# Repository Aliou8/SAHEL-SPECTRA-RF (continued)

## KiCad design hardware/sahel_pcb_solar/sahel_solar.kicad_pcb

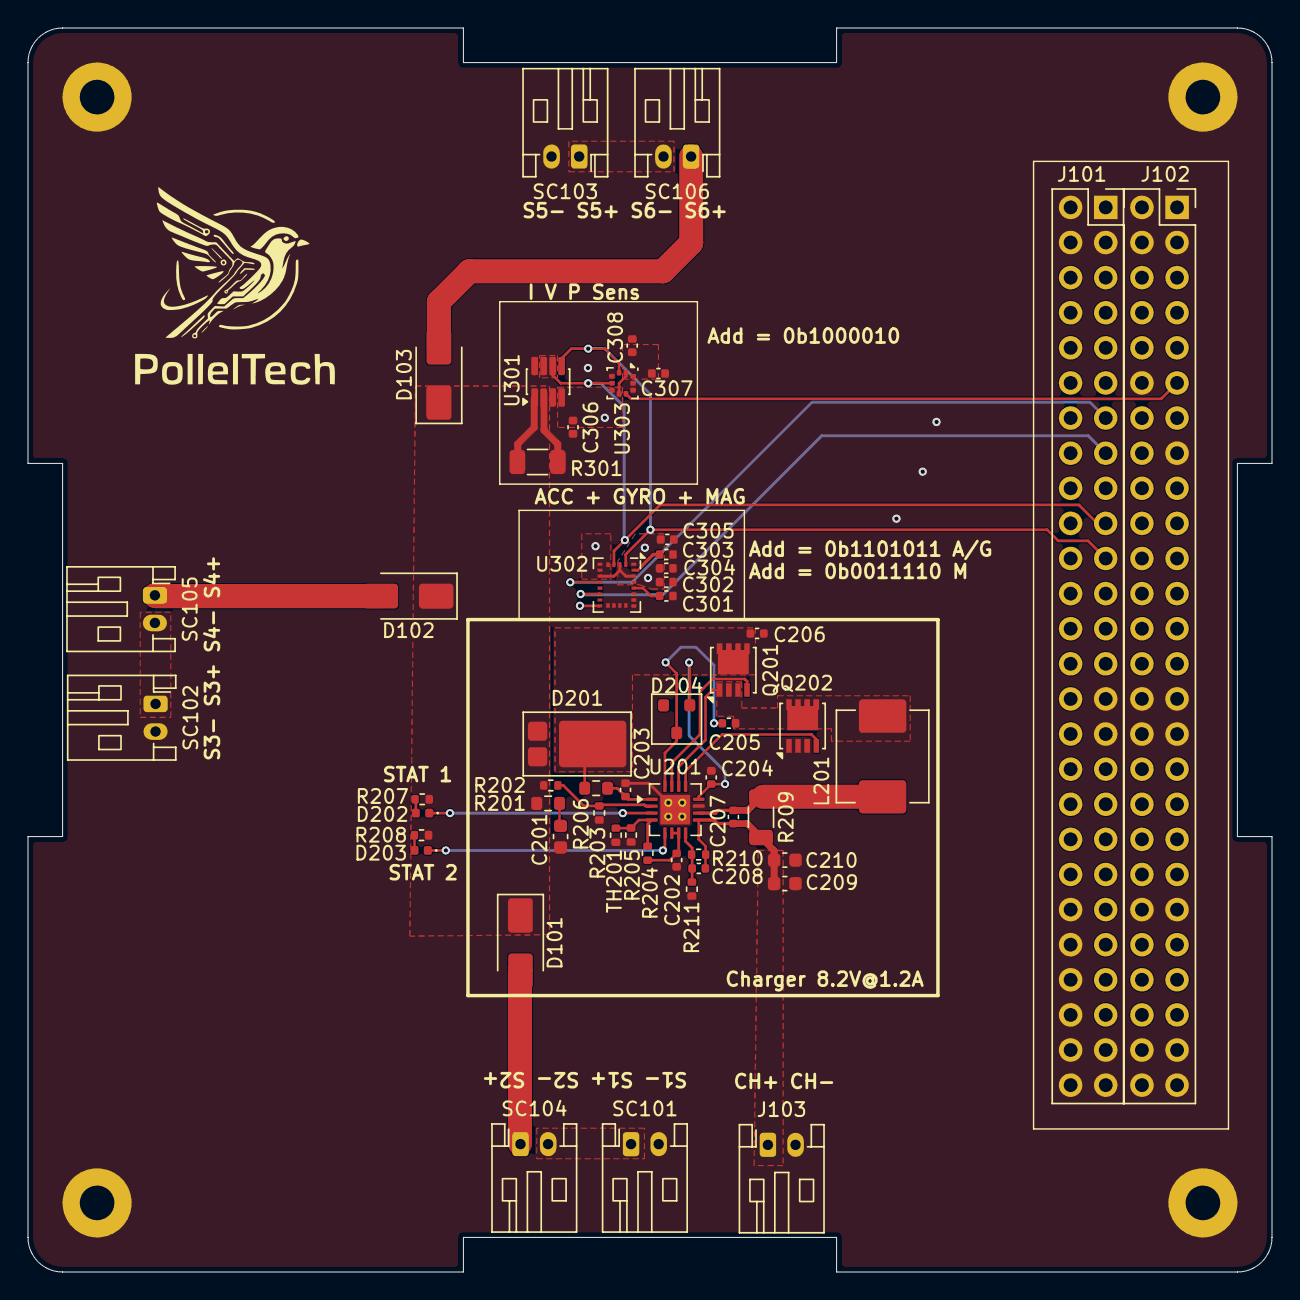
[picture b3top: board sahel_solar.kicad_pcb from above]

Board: 2 copper layers, 90.0 x 90.0 mm, 58 parts (0 on the bottom side), 34 nets.

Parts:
C201: 2.2u; C_0603_1608Metric
C202, C203, C204, C205, C206, C207, C302, C303, C305: 0.1u; C_0402_1005Metric
C208: 22p; C_0402_1005Metric
C209, C210: 10u; C_0603_1608Metric
C301: 10n; C_0402_1005Metric
C304: 10u; C_0402_1005Metric
C306, C307, C308: 1u; C_0402_1005Metric
D101, D102, D103: SS110; D_SMA
D201: PDS3100; D_PowerDI-5
D202: LED_S1; LED_0402_1005Metric
D203: LED_S2; LED_0402_1005Metric
D204: BAT54; SOT-23
H301, H302, H303, H304: MountingHole_Pad; MountingHole_2.5mm_Pad
J101, J102: Conn_02x26_Odd_Even; PinSocket_2x26_P2.54mm_Vertical
J103: charge; JST_PH_S2B-PH-K_1x02_P2.00mm_Horizontal
L201: 4.7u; L_Vishay_IHLP-2525
Q201, Q202: SiS454DN; Vishay_PowerPAK_1212-8_Single
R201: 2; R_0603_1608Metric
R202: 650k; R_0402_1005Metric
R203, R211: 100k; R_0402_1005Metric
R204: 9.31k; R_0402_1005Metric
R205: 430k; R_0402_1005Metric
R206: 10; R_0603_1608Metric
R207, R208: 10k; R_0402_1005Metric
R209, R301: 10m; R_1206_3216Metric
R210: 290k; R_0402_1005Metric
SC101, SC102, SC103, SC104, SC105, SC106: Solar_Cell; JST_PH_S2B-PH-K_1x02_P2.00mm_Horizontal
TH201: NTC; R_0402_1005Metric
U201: BQ24650; Texas_RVA_VQFN-16-1EP_3.5x3.5mm_P0.5mm_EP2.14x2.14mm_Therma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
U301: INA219AxDCN; SOT-23-8
U302: LSM9DS1; LGA-24L_3x3.5mm_P0.43mm
U303: LPS22HH; ST_HLGA-10_2x2mm_P0.5mm_LayoutBorder3x2y

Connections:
+3.3V: C302.1, C304.1, C305.1, C306.1, C307.1, C308.1, J101.5, J101.6, J101.11, J101.12, J101.17, J101.18, J101.23, J101.27, J101.28, J101.30, J101.33, J101.40, J101.47, J102.9, J102.10, J102.18, J102.21, J102.23, J102.25, J102.27, J102.28, J102.37, J102.38, J102.47, J102.48, U301.4 (VS), U302.1 (VDDIO), U302.3 (VDDIO), U302.5 (SDO_A/G), U302.6 (SDO_M), U302.7 (CS_A/G), U302.8 (CS_M), U302.13 (DEN_A/G), U302.22 (VDD), U302.23 (VDD), U303.1 (Vdd_IO), U303.5 (SA0), U303.6 (~CS), U303.10 (VDD)
/BUS_SCL: J101.21, U301.5 (SCL), U302.2 (SCL/SPC), U303.2 (SCL)
/BUS_SDA: J101.19, U301.6 (SDA), U301.7 (A0), U302.4 (SDA/SDI/SDO), U303.4 (SDA)
/CHARGER/LODRV: Q202.4 (G), U201.13 (LODRV)
/CHARGER/Pack+: C207.2, C208.2, C209.2, C210.2, J103.1, R209.2, R210.1, U201.9 (SRN)
/CHARGER/TS: R204.2, R205.1, TH201.1, U201.4 (TS)
/CHARGER/VFB: C208.1, R210.2, R211.1, U201.8 (VFB)
/DRDY_INT_B: J102.11, U303.7 (INT_DRDY)
/DRDY_M: J101.13, U302.9 (DRDY_M)
/INT_A/G: J101.15, U302.11 (INT1_A/G)
/SOLAR+: D101.1 (K), D102.1 (K), D103.1 (K), D201.2 (A), R201.2, R202.1, R207.2, R208.2, R301.2, U301.1 (IN+)
GND: C201.1, C202.1, C203.1, C204.1, C206.1, C209.1, C210.1, C301.2, C302.2, C303.2, C304.2, C305.2, C306.2, C307.2, C308.2, H301.1 (1_1), H302.1 (1_1), H303.1 (1_1), H304.1 (1_1), J101.1, J101.2, J101.3, J101.4, J101.29, J101.31, J101.42, J101.44, J101.46, J101.48, J101.49, J101.50, J101.51, J101.52, J102.1, J102.2, J102.3, J102.4, J102.12, J102.15, J102.29, J102.30, J102.31, J102.32, J102.41, J102.42, J102.49, J102.50, J102.51, J102.52, J103.2, Q202.1 (S), Q202.2 (S), Q202.3 (S), R203.2, R205.2, R211.2, R301.1, SC101.2 (-), SC102.2 (-), SC103.2 (-), TH201.2, U201.11 (GND), U201.17 (GND), U301.2 (IN-), U301.3 (GND), U301.8 (A1), U302.14 (RES), U302.15 (RES), U302.16 (RES), U302.17 (RES), U302.18 (RES), U302.19 (GND), U302.20 (GND), U303.3 (GND), U303.8 (GND), U303.9 (GND)
unnamed: C201.2, R201.1
unnamed: D101.2 (A), SC104.1 (+)
unnamed: D102.2 (A), SC105.1 (+)
unnamed: D103.2 (A), SC106.1 (+)
unnamed: C206.2, D201.1 (K), Q201.5 (D), R206.1
unnamed: D202.2 (A), R207.1
unnamed: D202.1 (K), U201.3 (STAT1)
unnamed: D203.2 (A), R208.1
unnamed: D203.1 (K), U201.5 (STAT2)
unnamed: C204.2, D204.1 (A), U201.12 (REGN)
unnamed: C205.1, D204.3 (K), U201.16 (BTST)
unnamed: Q201.4 (G), U201.15 (HIDRV)
unnamed: C205.2, L201.1, Q201.1 (S), Q201.2 (S), Q201.3 (S), Q202.5 (D), U201.14 (PH)
unnamed: SC101.1 (+), SC104.2 (-)
unnamed: SC102.1 (+), SC105.2 (-)
unnamed: SC103.1 (+), SC106.2 (-)
unnamed: R202.2, R203.1, U201.2 (MPPSET)
unnamed: C207.1, L201.2, R209.1, U201.10 (SRP)
unnamed: C202.2, R204.1, U201.6 (VREF), U201.7 (TERM_EN)
unnamed: C203.2, R206.2, U201.1 (VCC)
unnamed: C303.1, U302.24 (C1)
unnamed: C301.1, U302.21 (CAP)

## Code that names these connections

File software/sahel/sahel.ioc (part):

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Mcu.Name=STM32H7B0VBTx
Mcu.Package=LQFP100
Mcu.UserName=STM32H7B0VBTx
PA0.GPIOParameters=GPIO_Label
PA0.GPIO_Label=RF_EN
PA0.Signal=GPIO_Output
PA1.GPIOParameters=GPIO_Label
PA1.GPIO_Label=LED1
PA1.Signal=GPIO_Output
PA11.Mode=Host_FS
PA11.Signal=USB_OTG_HS_DM
PA12.Mode=Host_FS
PA12.Signal=USB_OTG_HS_DP
PA13.Mode=Trace_Asynchronous_SW
PA13.Signal=DEBUG_JTMS-SWDIO
PA14.Mode=Trace_Asynchronous_SW
PA14.Signal=DEBUG_JTCK-SWCLK
PA15.GPIOParameters=GPIO_Label
PA15.GPIO_Label=CAN_SHDN
PA15.Signal=GPIO_Output
PA2.GPIOParameters=GPIO_Label
PA2.GPIO_Label=LED2
PA2.Signal=GPIO_Output
PA3.GPIOParameters=GPIO_Label
PA3.GPIO_Label=LED3
PA3.Signal=GPIO_Output
PA4.Mode=NSS_Signal_Hard_Output
PA4.Signal=SPI1_NSS
PA5.Mode=Full_Duplex_Master
PA5.Signal=SPI1_SCK
PA6.Mode=Full_Duplex_Master
PA6.Signal=SPI1_MISO
PA7.Mode=Full_Duplex_Master
PA7.Signal=SPI1_MOSI
PA8.Mode=I2C
PA8.Signal=I2C3_SCL
PA9.GPIOParameters=GPIO_Label
PA9.GPIO_Label=FRAM_WP
PA9.Signal=GPIO_Output
PB10.GPIOParameters=GPIO_Label
PB10.GPIO_Label=VHF_GPIO1
PB10.Signal=GPIO_Output
PB12.Mode=NSS_Signal_Hard_Output
PB12.Signal=SPI2_NSS
PB13.Mode=Full_Duplex_Master
PB13.Signal=SPI2_SCK
PB14.Mode=Full_Duplex_Master
PB14.Signal=SPI2_MISO
PB15.Mode=Full_Duplex_Master
PB15.Signal=SPI2_MOSI
PB3.Mode=Trace_Asynchronous_SW
PB3.Signal=DEBUG_JTDO-SWO
PB4.GPIOParameters=GPIO_Label
PB4.GPIO_Label=RTC_EVI
PB4.Signal=GPIO_Output
PB5.GPIOParameters=GPIO_Label
PB5.GPIO_Label=RTC_INT
PB5.Signal=GPIO_Output
PB6.Mode=I2C
PB6.Signal=I2C1_SCL
PB7.Mode=I2C
PB7.Signal=I2C1_SDA
PC14-OSC32_IN.Mode=LSE-External-Clock-Source
PC14-OSC32_IN.Signal=RCC_OSC32_IN
PC4.GPIOParameters=GPIO_Label
PC4.GPIO_Label=UHF_GPIO1
PC4.Signal=GPIO_Output
PC5.GPIOParameters=GPIO_Label
PC5.GPIO_Label=UHF_GPIO2
PC5.Signal=GPIO_Output
PC9.Mode=I2C
PC9.Signal=I2C3_SDA
PD0.Mode=FDCAN_Activate
PD0.Signal=FDCAN1_RX
PD1.Mode=FDCAN_Activate
PD1.Signal=FDCAN1_TX
PD12.Mode=I2C
PD12.Signal=I2C4_SCL
PD13.Mode=I2C
PD13.Signal=I2C4_SDA
PD14.Mode=Asynchronous
PD14.Signal=UART9_RX
PD15.Mode=Asynchronous
PD15.Signal=UART9_TX
PD2.GPIOParameters=GPIO_Label
PD2.GPIO_Label=CAN_STB
PD2.Signal=GPIO_Output
PD4.Mode=Hardware Flow Control (RS485)
PD4.Signal=USART2_DE
PD5.Mode=Asynchronous
PD5.Signal=USART2_TX
PD6.Mode=Asynchronous
PD6.Signal=USART2_RX
PD8.GPIOParameters=GPIO_Label
PD8.GPIO_Label=SPI_CS2
PD8.Signal=GPIO_Output
PD9.GPIOParameters=GPIO_Label
PD9.GPIO_Label=SPI_CS3
PD9.Signal=GPIO_Output
PE11.Mode=NSS_Signal_Hard_Output
PE11.Signal=SPI4_NSS
PE12.Mode=Full_Duplex_Master
PE12.Signal=SPI4_SCK
PE13.Mode=Full_Duplex_Master
PE13.Signal=SPI4_MISO
PE14.Mode=Full_Duplex_Master
PE14.Signal=SPI4_MOSI
PE15.GPIOParameters=GPIO_Label
PE15.GPIO_Label=VHF_GPIO2
PE15.Signal=GPIO_Output
PH0-OSC_IN.Mode=HSE-External-Oscillator
PH0-OSC_IN.Signal=RCC_OSC_IN
PH1-OSC_OUT.Mode=HSE-External-Oscillator
PH1-OSC_OUT.Signal=RCC_OSC_OUT
RCC.HSE_VALUE=8000000
RCC.SYSCLKFreq_VALUE=280000000
RCC.SYSCLKSource=RCC_SYSCLKSOURCE_PLLCLK
board=custom

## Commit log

2026-05-09 feat(hardware): complete major CubeSat hardware milestone
    Finalize most PCB designs for OBC, radio, power, and solar interfaces
    Complete main mechanical structure design of the CubeSat
    Generate STM32CubeMXIDE software project for STM32H7 platform
    Prepare hardware/software integration baseline for future development
2026-05-09 docs: advance README documentation
2026-05-10 docs: advance README documentation
    Remove KiCad project files for sahel_pcb and its subprojects, indicating a clean slate for future development. Mark subprojects as dirty to reflect uncommitted changes.
2026-05-11 docs: advance README documentation
    Refactor code structure for improved readability and maintainability
2026-05-16 Add support for Sahel STM32H7B0 board and associated drivers
    - Created device tree source (DTS) file for Sahel STM32H7B0 board with configurations for GPIO, UART, SPI, I2C, CAN, and various sensors.
    - Added YAML configuration for the Sahel STM32H7B0 board, specifying memory and supported features.
    - Introduced default configuration file for the board enabling MPU, stack protection, and GPIO.
    - Implemented CMake and Kconfig files for BQ76907 battery protection module, including driver source and bindings.
    - Added CC1125 radio transceiver module with necessary configurations and driver files.
    - Integrated FM24CL64B I2C FRAM module with complete driver implementation and device tree bindings.
2026-05-19 Add BQ76907 driver implementation and remove CC1125 module
    - Implemented the BQ76907 driver in `bq76907.h` with necessary data structures, error codes, and sensor channels.
    - Updated device tree bindings for BQ76907 in `ti,bq76907.yml` to include new properties for voltage and current thresholds.
    - Removed the CC1125 module, including its drivers, Kconfig, and device tree bindings, as it is no longer needed.
    - Added a Kconfig dependency for EEPROM in the FM24CL64B driver.
    - Created a new README.md file for documentation purposes.
2026-05-19 chore: bump version to v0.0.2
2026-05-19 Refactor code structure for improved readability
